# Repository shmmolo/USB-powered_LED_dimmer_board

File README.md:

# USB-Powered LED Dimmer Board

A compact USB-powered LED dimmer using a 555 timer in astable mode to generate PWM for LED brightness control. Built with KiCad and designed for learning, testing, and prototyping.

## Features
- 5V USB input with polyfuse and ESD protection
- Adjustable PWM (up to 1.2 kHz)
- NMOS transistor output stage for LED strips
- Compact 2-layer PCB layout

## Components
- **U1:** USBLC6-2SC6 (ESD Protection)
- **F1:** Polyfuse 555
- **U2:** NE555P Timer
- **Q1:** N-channel MOSFET
- **D1, D2:** Diodes (Protection & Indicator)
- **R1–R5, C1–C2:** Timing and filtering components

## How It Works
PWM duty cycle from the NE555 determines LED brightness. The NMOS transistor switches the LED strip according to PWM output, with frequency beyond visible flicker range.

## Applications
- USB LED dimmer
- PWM circuit learning
- Small electronics projects

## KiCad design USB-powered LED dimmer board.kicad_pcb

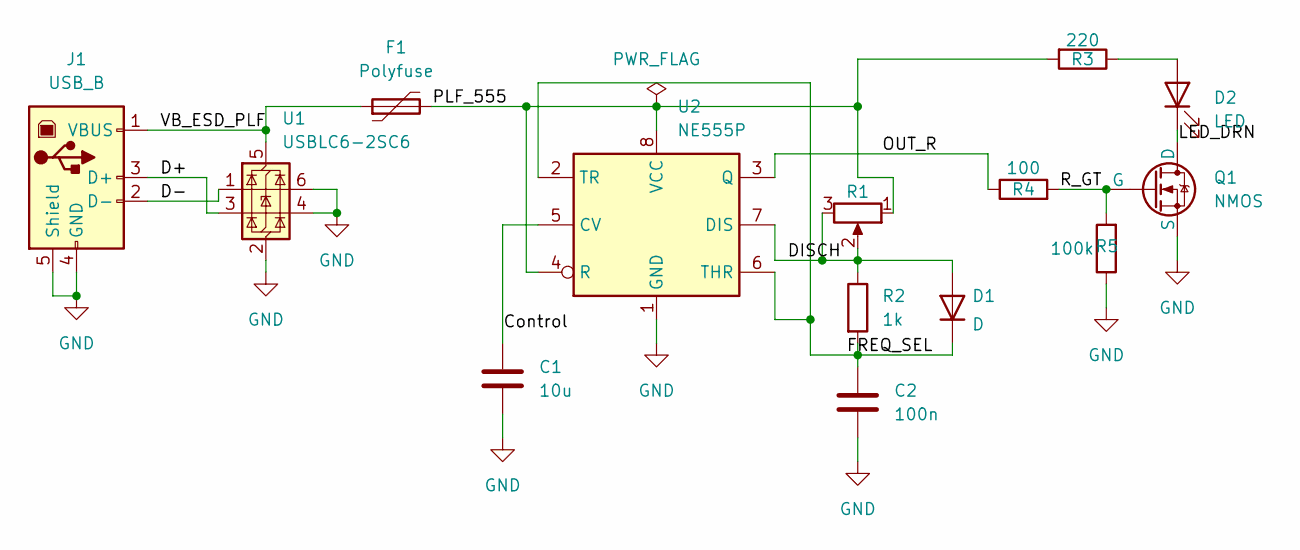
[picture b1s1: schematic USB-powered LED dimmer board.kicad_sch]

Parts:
C1: 10u; C_Disc_D4.3mm_W1.9mm_P5.00mm
C2: 100n; C_Disc_D4.3mm_W1.9mm_P5.00mm
D1: D; D_A-405_P7.62mm_Horizontal
D2: LED; LED_D5.0mm
F1: Polyfuse; Fuse_Bourns_MF-RHT050
J1: USB_B; USB_Mini-B_Lumberg_2486_01_Horizontal
Q1: NMOS; SOT-23
R1: R_Potentiometer; Potentiometer_ACP_CA6-H2,5_Horizontal
R2: 1k; R_Axial_DIN0207_L6.3mm_D2.5mm_P7.62mm_Horizontal
R3: 220; R_Axial_DIN0207_L6.3mm_D2.5mm_P7.62mm_Horizontal
R4: 100; R_Axial_DIN0207_L6.3mm_D2.5mm_P7.62mm_Horizontal
R5: 100k; R_Axial_DIN0207_L6.3mm_D2.5mm_P7.62mm_Horizontal
U1: USBLC6-2SC6; SOT-23-6
U2: NE555P; DIP-8_W7.62mm

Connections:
/Control: C1.1, U2.5 (CV)
/D+: J1.3 (D+), U1.3 (I/O2)
/D-: J1.2 (D-), U1.1 (I/O1)
/DISCH: D1.2 (A), R1.2, R1.3, R2.1, U2.7 (DIS)
/FREQ_SEL: C2.1, D1.1 (K), R2.2, U2.2 (TR), U2.6 (THR)
/LED_DRN: D2.1 (K), Q1.1 (D)
/OUT_R: R4.1, U2.3 (Q)
/PLF_555: F1.2, R1.1, R3.2, U2.4 (R), U2.8 (VCC)
/R_GT: Q1.2 (G), R4.2, R5.2
/VB_ESD_PLF: F1.1, J1.1 (VBUS), U1.5 (VBUS)
GND: C1.2, C2.2, J1.4 (GND), J1.5 (Shield), Q1.3 (S), R5.1, U1.2 (GND), U1.4 (I/O2), U1.6 (I/O1), U2.1 (GND)
unnamed: D2.2 (A), R3.1

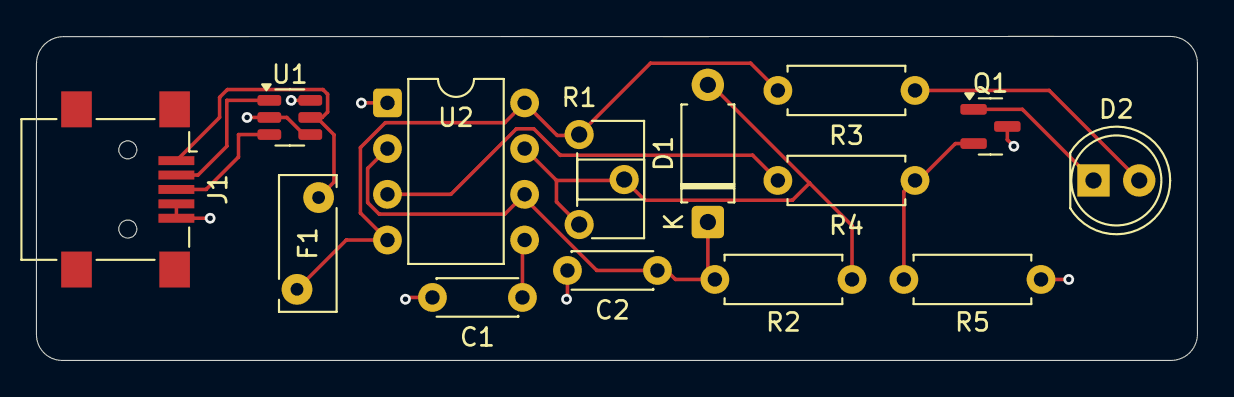
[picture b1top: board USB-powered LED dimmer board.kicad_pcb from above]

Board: 2 copper layers, 64.5 x 18.0 mm, 14 parts (0 on the bottom side), 12 nets.

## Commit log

2025-10-29 README.md
2025-10-29 Added to Hardware
2025-10-29 Added to Docs
